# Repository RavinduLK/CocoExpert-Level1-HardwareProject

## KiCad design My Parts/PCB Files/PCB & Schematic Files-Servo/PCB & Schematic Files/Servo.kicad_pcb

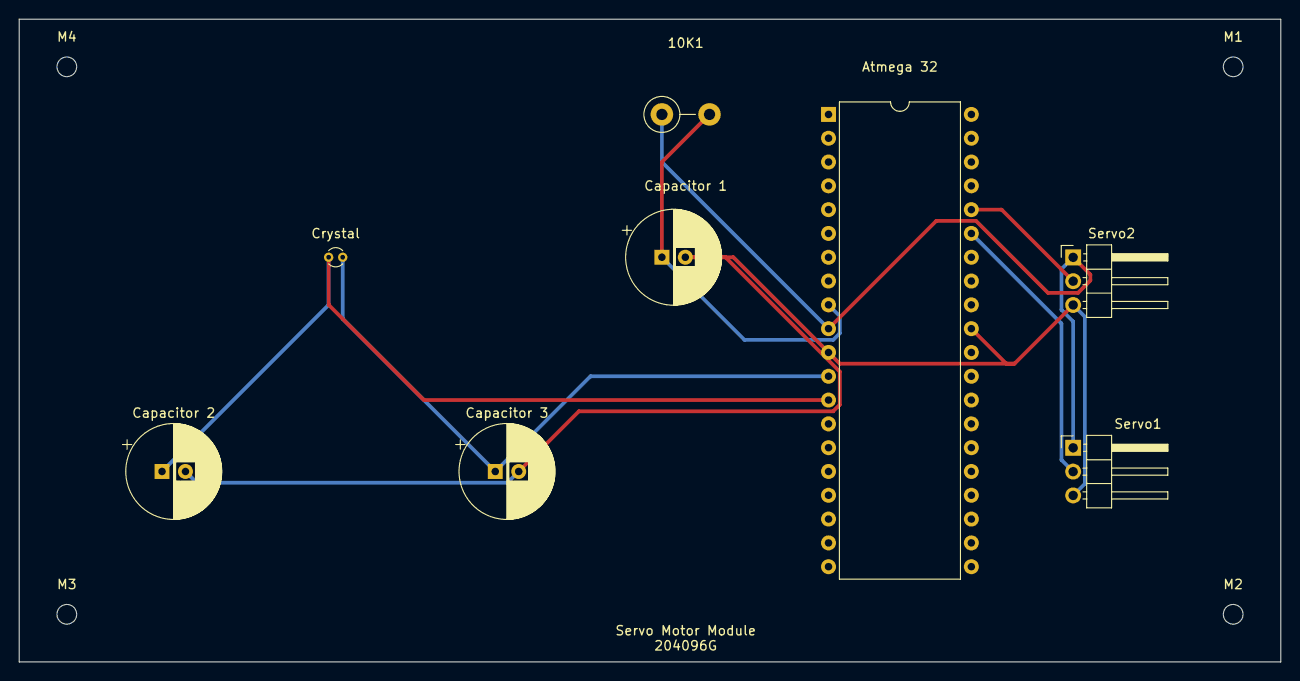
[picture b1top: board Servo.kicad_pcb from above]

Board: 2 copper layers, 134.6 x 68.6 mm, 12 parts (0 on the bottom side), 7 nets.

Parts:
10K1: Resistor; R_Axial_DIN0411_L9.9mm_D3.6mm_P5.08mm_Vertical
Atmega 32: ATmega32A-P; DIP-40_W15.24mm
Capacitor 1: 1uF; CP_Radial_D10.0mm_P2.50mm
Capacitor 2, Capacitor 3: 22pF; CP_Radial_D10.0mm_P2.50mm
Crystal: Y1; Crystal_DS10_D1.0mm_L4.3mm_Vertical
M1, M2, M3, M4: MountingHole_2.1mm
Servo1, Servo2: Conn_01x03; PinHeader_1x03_P2.54mm_Horizontal

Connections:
+5V: 10K1.1, Atmega 32.10 (VCC), Servo1.1, Servo2.1
Earth: Atmega 32.11 (GND), Atmega 32.31 (GND), Capacitor 1.2, Capacitor 2.2, Capacitor 3.2, Servo1.3, Servo2.3
unnamed: 10K1.2, Atmega 32.9 (~RESET), Capacitor 1.1
unnamed: Atmega 32.13 (XTAL1), Capacitor 2.1, Crystal.1
unnamed: Atmega 32.12 (XTAL2), Capacitor 3.1, Crystal.2
unnamed: Atmega 32.35 (PA5), Servo1.2
unnamed: Atmega 32.36 (PA4), Servo2.2

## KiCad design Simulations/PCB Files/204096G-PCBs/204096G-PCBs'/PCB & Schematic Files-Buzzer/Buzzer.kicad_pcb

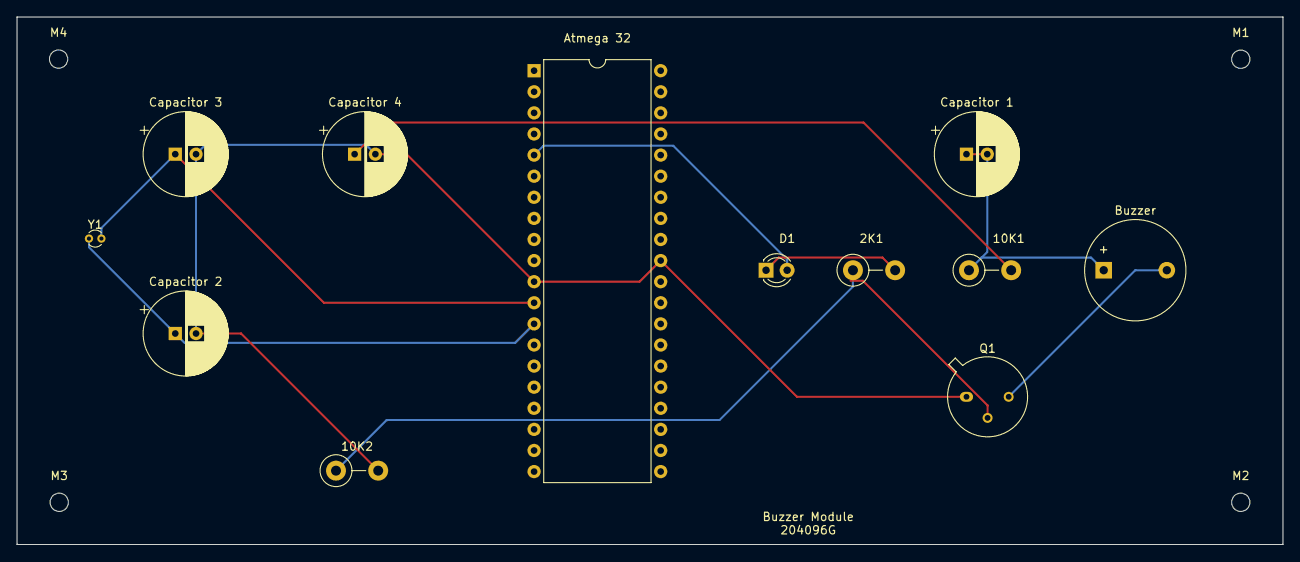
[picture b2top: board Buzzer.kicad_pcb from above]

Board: 2 copper layers, 152.4 x 63.5 mm, 16 parts (0 on the bottom side), 9 nets.

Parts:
2K1: Resistor 1; R_Axial_DIN0411_L9.9mm_D3.6mm_P5.08mm_Vertical
10K1: Resistor 2; R_Axial_DIN0411_L9.9mm_D3.6mm_P5.08mm_Vertical
10K2: Resistor 3; R_Axial_DIN0411_L9.9mm_D3.6mm_P5.08mm_Vertical
Atmega 32: ATmega32A-P; DIP-40_W15.24mm
Buzzer: Buzzer; Buzzer_12x9.5RM7.6
Capacitor 1: 4.7uF; CP_Radial_D10.0mm_P2.50mm
Capacitor 2, Capacitor 3: 22pF; CP_Radial_D10.0mm_P2.50mm
Capacitor 4: 1uF; CP_Radial_D10.0mm_P2.50mm
D1: LED; LED_D3.0mm
M1, M2, M3, M4: MountingHole_2.2mm_M2
Q1: NPN Transistor; TO-39-3
Y1: Crystal; Crystal_DS10_D1.0mm_L4.3mm_Vertical

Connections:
+6V: 10K1.1, Buzzer.1 (-), Capacitor 1.1, Capacitor 1.2
Earth: 10K2.2, Atmega 32.11 (GND), Atmega 32.31 (GND), Capacitor 2.2, Capacitor 3.2, Capacitor 4.2, Q1.1 (E)
unnamed: 10K1.2, Capacitor 4.1
unnamed: 2K1.1, 10K2.1, Q1.2 (B)
unnamed: 2K1.2, D1.1 (K)
unnamed: Atmega 32.13 (XTAL1), Capacitor 2.1, Y1.1
unnamed: Atmega 32.12 (XTAL2), Capacitor 3.1, Y1.2
unnamed: Buzzer.2 (+), Q1.3 (C)
unnamed: Atmega 32.5 (PB4), D1.2 (A)
